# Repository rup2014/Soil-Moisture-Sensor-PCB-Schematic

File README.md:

# SoilMoistureReaderDesign

This project contains the KiCad schematic and PCB layout for a soil moisture reader built around the ESP32-WROVER module.

## Features

- **ESP32-WROVER Based**: Utilizes the powerful ESP32-WROVER 
- **Programming Header**: A 4x1 header enables convenient programming of the ESP32.
- **OLED Display Support**: A second 4x1 header is provided for connecting an SSD1306 OLED display to show real-time readings.
- **Enable Button**: Used in conjuction with programming header to flash the ESP32.
- **Manual Scan Button**: Includes a button allowing users to manually trigger soil moisture scans.

## Hardware Overview

- **Microcontroller**: ESP32-WROVER
- **Display**: SSD1306 OLED (via header)
- **Programming Interface**: 4x1 header
- **Enable/Reset Button**: Enable Flash/Reset button
- **User Input**: Manual scan button

## Getting Started

1. **Clone the Repository**
   ```
   git clone https://github.com/rup2014/SoilMoistureReaderDesign.git
   ```
2. **Open the KiCad Project**
   - Launch KiCad and open the project files in this repository.
3. **Review Schematics and PCB**
   - Schematics and PCB files are provided for hardware fabrication and modification.

## Usage

- Connect the ESP32-WROVER and SSD1306 OLED as indicated in the schematic.
- Use the programming header for firmware uploads.
- Use the manual scan switch to initiate readings.

## License

This project is open-source. See the LICENSE file for more details.

## Author

- Maintained by [rup2014](https://github.com/rup2014)

---

*For questions or contributions, feel free to open an issue or pull request.*

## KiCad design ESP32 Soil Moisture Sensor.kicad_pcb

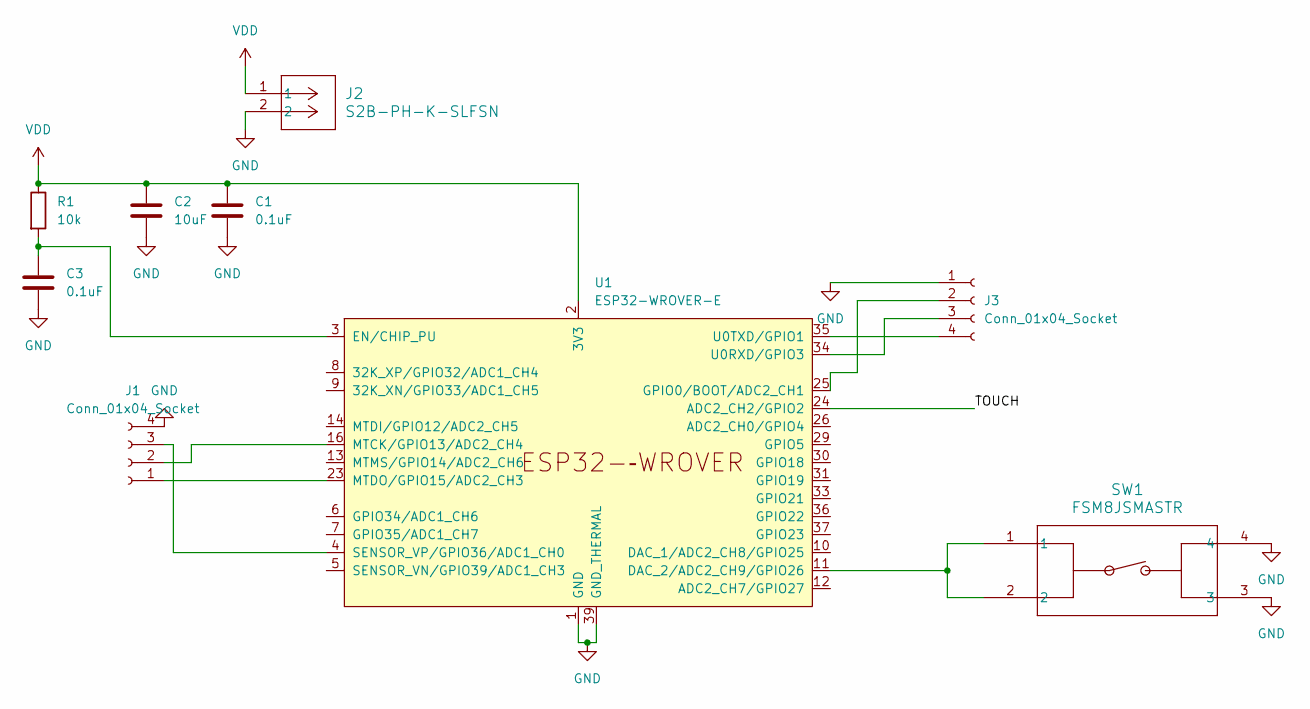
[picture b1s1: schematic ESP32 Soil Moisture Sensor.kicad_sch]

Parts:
C1, C3: 0.1uF; C_0201_0603Metric
C2: 10uF; C_0201_0603Metric
J1, J3: Conn_01x04_Socket; FanPinHeader_1x04_P2.54mm_Vertical
J2: S2B-PH-K-SLFSN; CONN_S2B-PH-K-S_JST
R1: 10k; R_0201_0603Metric
SW1: FSM8JSMASTR; SW4_FSM8JSMASTR_TEC
U1: ESP32-WROVER-E

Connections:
/TOUCH: U1.24 (ADC2_CH2/GPIO2)
GND: C1.2, C2.2, C3.2, J1.4, J2.2, J3.1, SW1.3, SW1.4, U1.1 (GND), U1.15 (GND), U1.38 (GND), U1.39 (GND_THERMAL)
unnamed: J1.1, U1.23 (MTDO/GPIO15/ADC2_CH3)
unnamed: J1.2, U1.16 (MTCK/GPIO13/ADC2_CH4)
unnamed: J1.3, U1.4 (SENSOR_VP/GPIO36/ADC1_CH0)
unnamed: J3.2, U1.25 (GPIO0/BOOT/ADC2_CH1)
unnamed: J3.3, U1.34 (U0RXD/GPIO3)
unnamed: J3.4, U1.35 (U0TXD/GPIO1)
unnamed: SW1.1, SW1.2, U1.11 (DAC_2/ADC2_CH9/GPIO26)
unnamed: C3.1, R1.2, U1.3 (EN/CHIP_PU)
VDD: C1.1, C2.1, J2.1, R1.1, U1.2 (3V3)

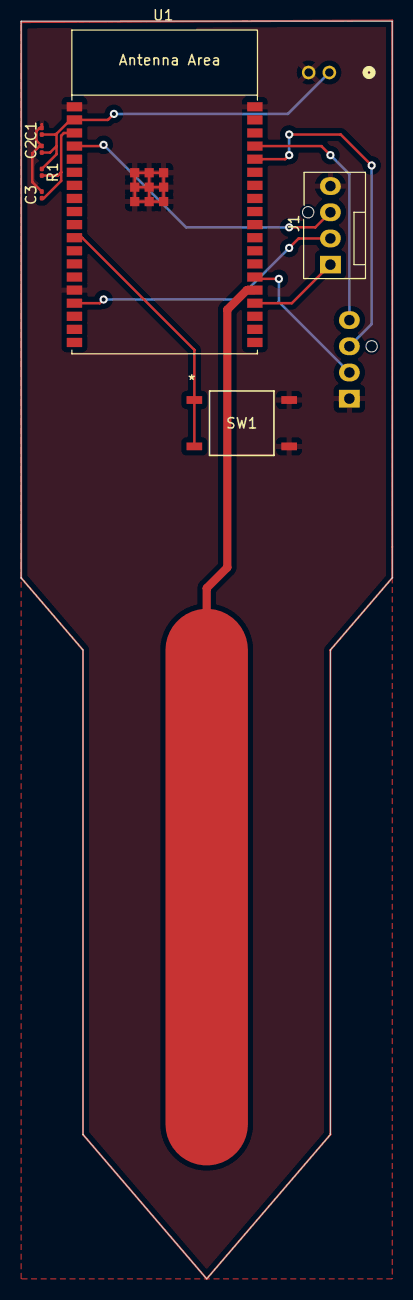
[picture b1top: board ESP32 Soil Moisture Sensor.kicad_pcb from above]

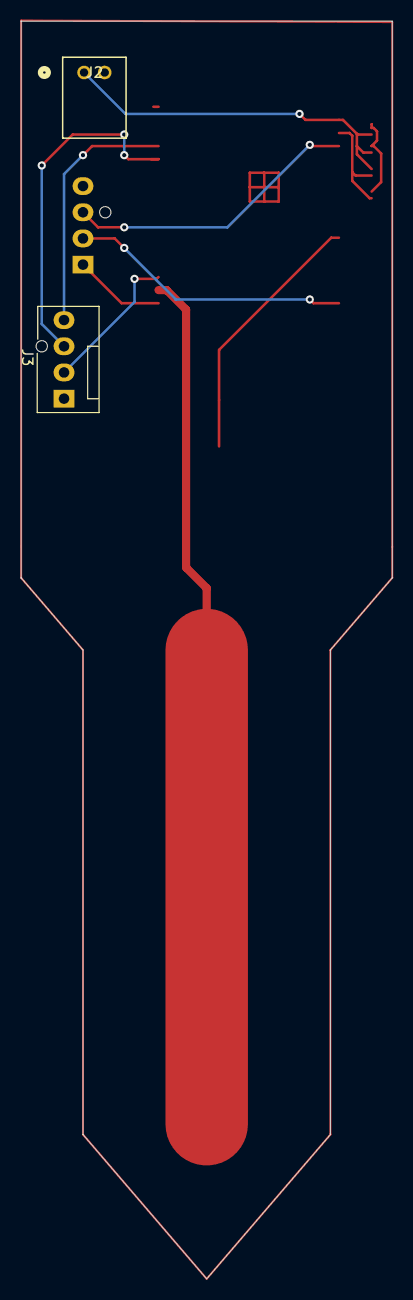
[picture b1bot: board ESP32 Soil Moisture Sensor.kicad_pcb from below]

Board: 2 copper layers, 36.0 x 122.0 mm, 9 parts (2 on the bottom side), 10 nets.

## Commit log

2024-01-29 not sure
